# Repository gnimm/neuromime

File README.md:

The “neuromime” is an electronic model of an organic nerve cell that can be interconnected in chains and loops. It is released here as an open-source hardware project in a collaborative effort by artists Norman White (original concept and design) and Peter Flemming (revision, expansion). Neuromimes are intended for (but not limited to) use in the creation of electro-physical artworks. Neuromimes can also function as the modular core of laboratory-style workshops where participants collectively generate an artwork for exhibition. Neuromimes are extensible building blocks, ideally suited to a collective making setting and/or generative, interactive artworks. Reminiscent of an exquisite corpse, they provide a framework that, while structured, is not scripted.

LINKS

Norman White speaking on the Neuromime at Interaccess (8'00"): https://www.youtube.com/watch?v=ue9ZF_hO-PE

Norman White on wikipedia: http://en.wikipedia.org/wiki/Norman_White

Norman White's website with other projects: http://normill.ca/

Peter Flemming's website with other projects: http://peterflemming.net

PROPERTIES OF AN ORGANIC NEURON

1. All-or-Nothing – It either fires completely or not at all (in this way it is "digital").

2. Temporal Summation – It can be made to fire by triggering one dendrite receptor repeatedly over time.

3. Spatial Summation – It can be made to fire by triggering several of its dendrite receptors simultaneously or virtually so.

4. Latency – It takes awhile for the impulse to travel from the dendrite receptor(s) along the axon to the output points (terminals).

5. Refractory Period – Once fired, it rests awhile before it can respond to stimuli again. 

TECHNICAL

-these folders contains files for a printed circuit board generated with KiCad, build: (2012-apr-16-27), http://www.kicad.org

-important technical annotation is contained in Norman's original schematic in the "ref" folder

-supplementary files (other schematics, visual information) are in the folder "ref"

-see the index below for detailed description of folder contents and files‎

INDEX (most folders have a detailed index as well)

1.0.0/

   ---this folder contains the Neuromime board files, schematics, fabrication outputs (Gerber etc.) done in KiCad

kicadlibs/

   ---folder contains footprint and schematic device libraries used in Neuromime not included in standard KiCad

ref/

   ---folder for supplementary files (Norman's original schematic, other visual information etc.)

LICENSE.txt

   ---Creative Commons license

README.md

   ---this file

TODO.txt

   ---errors, to do, future versions, suggestions, comments

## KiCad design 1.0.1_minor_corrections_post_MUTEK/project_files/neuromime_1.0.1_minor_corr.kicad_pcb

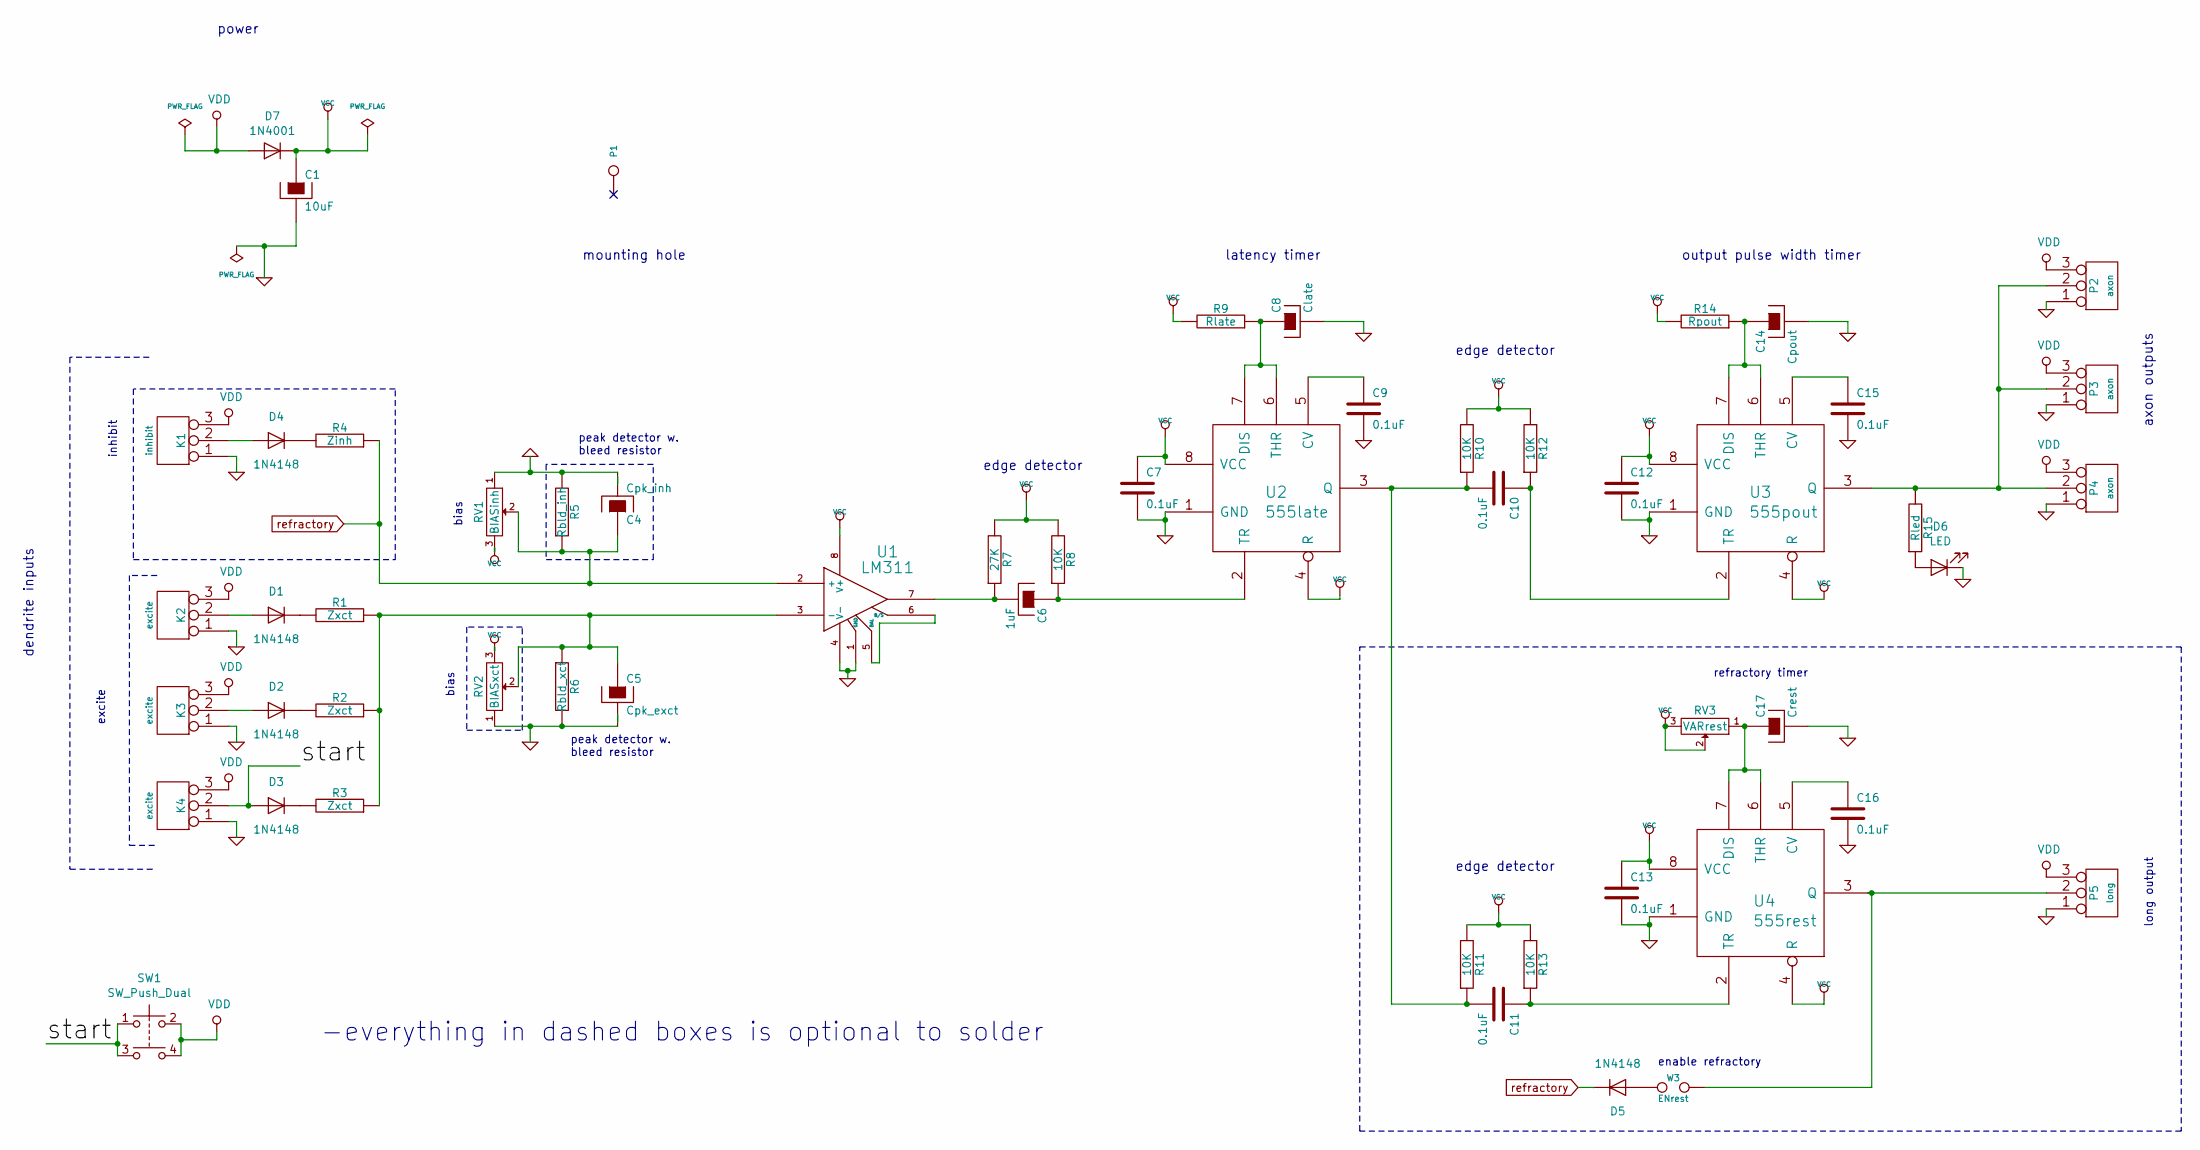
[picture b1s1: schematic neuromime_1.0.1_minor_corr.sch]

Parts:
C1: 10uF; CP_Radial_D5.0mm_P2.50mm_positive_symbol_inside
C4: Cpk_inh; CP_Radial_D5.0mm_P2.50mm_positive_symbol_inside
C5: Cpk_exct; CP_Radial_D5.0mm_P2.50mm_positive_symbol_inside
C6: 1uF; CP_Radial_D5.0mm_P2.50mm_positive_symbol_inside
C7, C9, C10, C11, C12, C13, C15, C16: 0.1uF; C_Disc_D3.0mm_W1.6mm_P2.50mm
C8: Clate; CP_Radial_D5.0mm_P2.50mm_positive_symbol_inside
C14: Cpout; CP_Radial_D5.0mm_P2.50mm_positive_symbol_inside_single_corr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
C17: Crest; CP_Radial_D5.0mm_P2.50mm_positive_symbol_inside
D1, D2, D3, D4, D5: 1N4148; D_DO-35_SOD27_P2.54mm_Vertical_KathodeUp
D6: LED; LED_D3.0mm
D7: 1N4001; D_DO-41_SOD81_P5.08mm_Vertical_KathodeUp
K1: inhibit; PinSocket_1x03_P2.54mm_Horizontal_elongated
K2, K3, K4: excite; PinSocket_1x03_P2.54mm_Horizontal_elongated
P1: mnt; MountingHole_4.5mm
P2, P3, P4: axon; PinHeader_1x03_P2.54mm_Horizontal_elomgated_pads
P5: long; PinHeader_1x03_P2.54mm_Horizontal_elomgated_pads
R1, R2, R3: Zxct; R_Axial_DIN0207_L6.3mm_D2.5mm_P2.54mm_Vertical_pad_numbers_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
R4: Zinh; R_Axial_DIN0207_L6.3mm_D2.5mm_P2.54mm_Vertical_pad_numbers_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
R5: Rbld_inh; R_Axial_DIN0204_L3.6mm_D1.6mm_P2.54mm_Vertical
R6: Rbld_xct; R_Axial_DIN0204_L3.6mm_D1.6mm_P2.54mm_Vertical
R7: 27K; R_Axial_DIN0204_L3.6mm_D1.6mm_P2.54mm_Vertical
R8, R10, R11, R12, R13: 10K; R_Axial_DIN0204_L3.6mm_D1.6mm_P2.54mm_Vertical
R9: Rlate; R_Axial_DIN0204_L3.6mm_D1.6mm_P2.54mm_Vertical
R14: Rpout; R_Axial_DIN0204_L3.6mm_D1.6mm_P2.54mm_Vertical
R15: Rled; R_Axial_DIN0204_L3.6mm_D1.6mm_P2.54mm_Vertical
RV1: BIASinh; Potentiometer_Bourns_3266W_Vertical_pin_variation
RV2: BIASxct; Potentiometer_Bourns_3266W_Vertical_pin_variation
RV3: VARrest; Potentiometer_Bourns_3266W_Vertical_pin_variation
SW1: SW_Push_Dual; SW_TH_Tactile_Omron_B3F-10xx
U1: LM311; DIP-8_W7.62mm_Socket
U2: 555late; DIP-8_W7.62mm_Socket
U3: 555pout; DIP-8_W7.62mm_Socket
U4: 555rest; DIP-8_W7.62mm_Socket
W3: ENrest; PinHeader_1x02_P2.54mm_Vertical

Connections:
/start: D3.2 (A), K4.2 (PM), SW1.1, SW1.3
GND: C1.2, C4.2, C5.2, C7.2, C8.2, C9.2, C12.2, C13.2, C14.2, C15.2, C16.2, C17.2, D6.1 (K), K1.1, K2.1, K3.1, K4.1, P2.1, P3.1, P4.1, P5.1, R5.2, R6.2, RV1.1, RV2.1, U1.1 (GND), U1.4 (V-), U2.1 (GND), U3.1 (GND), U4.1 (GND)
unnamed: C5.1, R1.1, R2.1, R3.1, R6.1, RV2.2, U1.3 (-)
unnamed: C6.1, R8.1, U2.2 (TR)
unnamed: C6.2, R7.1, U1.7
unnamed: C8.1, R9.1, U2.6 (THR), U2.7 (DIS)
unnamed: C9.1, U2.5 (CV)
unnamed: C10.1, R12.1, U3.2 (TR)
unnamed: C10.2, C11.2, R10.1, R11.1, U2.3 (Q)
unnamed: C11.1, R13.1, U4.2 (TR)
unnamed: C14.1, R14.1, U3.6 (THR), U3.7 (DIS)
unnamed: C15.1, U3.5 (CV)
unnamed: C16.1, U4.5 (CV)
unnamed: C17.1, RV3.1, U4.6 (THR), U4.7 (DIS)
unnamed: D1.1 (K), R1.2
unnamed: D1.2 (A), K2.2 (PM)
unnamed: D2.1 (K), R2.2
unnamed: D2.2 (A), K3.2 (PM)
unnamed: D3.1 (K), R3.2
unnamed: D4.1 (K), R4.2
unnamed: D4.2 (A), K1.2 (PM)
unnamed: D5.2 (A), W3.1
unnamed: D6.2 (A), R15.1
unnamed: P2.2 (PM), P3.2 (PM), P4.2 (PM), R15.2, U3.3 (Q)
unnamed: P5.2 (PM), U4.3 (Q), W3.2
unnamed: U1.5 (BAL), U1.6 (B/S)
VCC: C1.1, C7.1, C12.1, C13.1, D7.1 (K), R7.2, R8.2, R9.2, R10.2, R11.2, R12.2, R13.2, R14.2, RV1.3, RV2.3, RV3.2, RV3.3, U1.8 (V+), U2.4 (R), U2.8 (VCC), U3.4 (R), U3.8 (VCC), U4.4 (R), U4.8 (VCC)
VDD: D7.2 (A), K1.3, K2.3, K3.3, K4.3, P2.3, P3.3, P4.3, P5.3, SW1.2, SW1.4
refractory: C4.1, D5.1 (K), R4.1, R5.1, RV1.2, U1.2 (+)

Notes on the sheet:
mounting hole
dendrite inputs
axon outputs
power
edge detector
output pulse width timer
latency timer
inhibit
excite
bias
peak detector w. bleed resistor
enable refractory
refractory timer
long output
-everything in dashed boxes is optional to solder

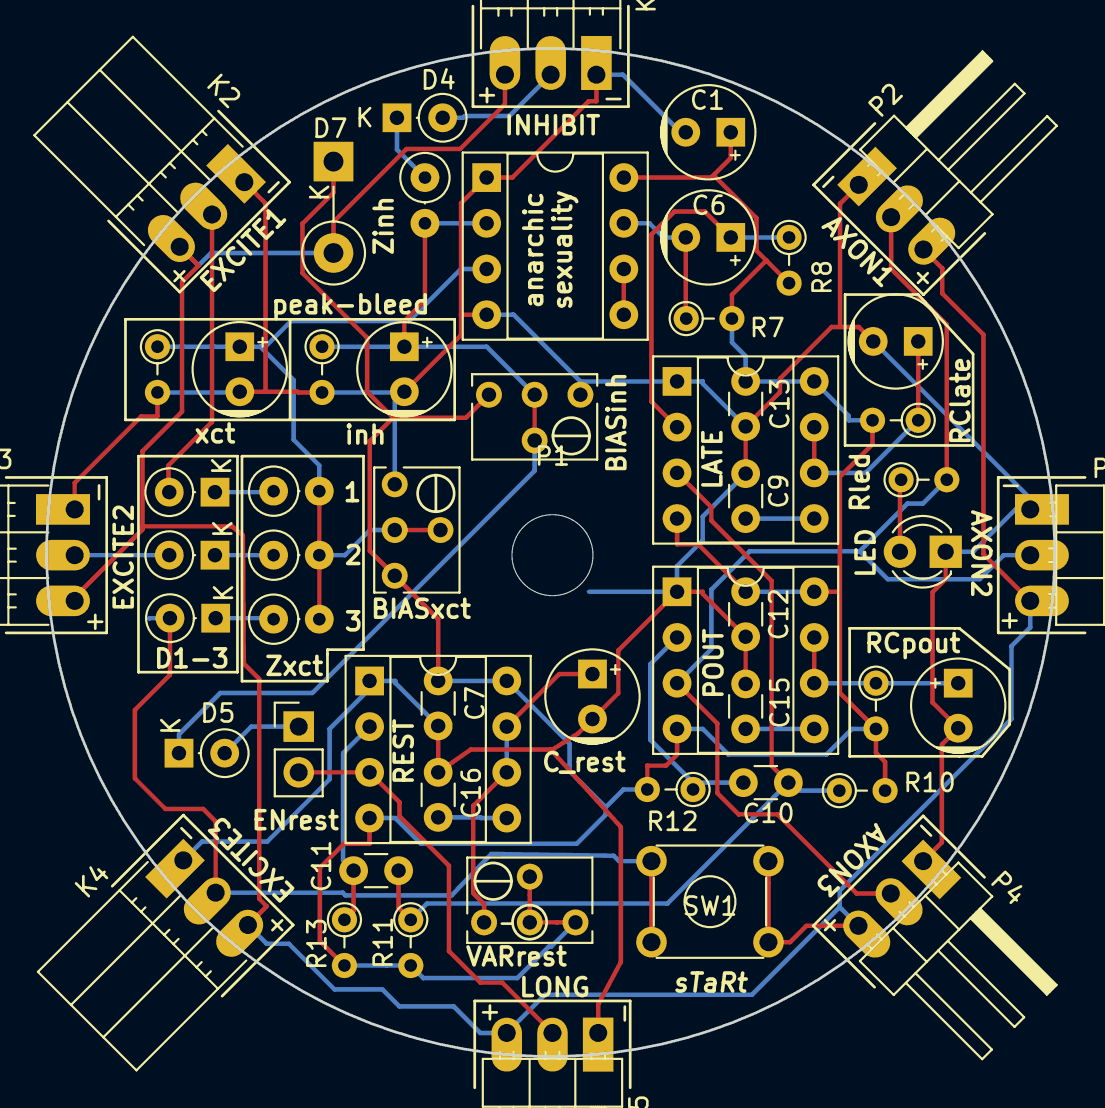
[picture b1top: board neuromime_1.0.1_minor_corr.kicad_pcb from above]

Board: 2 copper layers, 56.0 x 56.0 mm, 55 parts (0 on the bottom side), 29 nets.

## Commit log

2015-03-06 initialize
2015-03-06 added license
2015-03-17 clean up, add indexes, refs
2015-03-17 reformat readme
2015-03-17 remove ~ files
2015-03-17 edit todo
2015-09-01 new file: 1.0.0/BOM.txt modified: 1.0.0/INDEX.txt new file: 1.0.0/INDEX.txt~ renamed: 1.0.0/neuromime_1.0.0-cache.dcm -> 1.0.0/project_files/neuromime_1.0.0-cache.dcm renamed: 1.0.0/neuromime_1.0.0-c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
2015-09-01 minor edits
2015-09-01 first BOM
2016-08-07 adding 1.0.1
2016-08-14 Added initial pd simulator and changed simulator dir. structure
2016-08-14 ...changed simulator dir structure
2017-03-14 testing new clone
2017-03-14 testing, ignore
2017-03-14 starting smd version of board for EB residency
2017-03-30 added byteToTone.ino
2017-06-17 all kinds of new stuff, whatever
2017-06-17 Added some note to TODO about high speed neuromimes
2017-06-17 more adding of stuff and trying to use git properly
2017-06-17 added git cheat
2017-06-17 sounds good
2018-11-05 changed name of version 1.0.1 folder
2018-11-05 deleted 1.0.1 version folder, will attempt to properly branch
2018-11-05 creating 1.1.0 SMD/lowpower version
2019-06-29 (re) added folder for 1.0.1 to master branch, contains whiteboard sketches for schematic in _notes_ folder
2019-06-29 filename changes in 1.0.1/sketches
2019-06-29 rescuing accidentally deleted items in 1.0.1 folder
2019-06-29 added pdf version of schematic in folder 1.0.0
2019-07-06 work on 1.0.1, a simplified version w. optional refractory and inhibit complexes; pdf schematic in project folder
2019-07-06 work on 1.0.1 board; still messy; not routed
2019-07-06 work on 1.0.1 board; autoroute test
2019-07-07 work on 1.0.1; increase autoroute spacing to .5mm; labelling
2019-07-07 work on 1.0.1;housekeeping; paths; included footprints libs
2019-07-08 almost final version; added pcbfab renaming and zipping script to utils; libray management
2019-07-09 added LIF Neuron Arduino code
2019-07-09 added reverse power protection diode; cleaned up labels on board; production ready... just needs one last little looksee from Stephen :)
2019-07-17 BOM in project folder; as csv (possibly stale) and libreoffice spreadsheet (with links)
2019-07-26 changed 1.0. 1 to 1.0.1
2019-07-26 tidying up...
2019-07-26 removed 1.0_space_.1
2019-07-26 update BOM with board label cross reference
2019-07-27 generate current pdf schematic
2019-08-02 update BOM
2019-08-22 added a few notes after the Mutek exhibit
2021-11-08 Update README.md
    https://forum.kicad.info/t/warning-avoid-all-links-to-kicad-pcb-org-use-kicad-org/31521
